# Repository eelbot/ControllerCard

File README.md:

#Pico Commander
The Pico Commander is a Circuit to PC interface that runs programs created by a user 
in a drag and drop style desktop application. This is my capstone project, and is currently
undergoing a major redesign. Throughout the first version of the project I learned a 
lot, and am going to improve Pico Commander in several areas to reduce cost, increase
functionality, and better the user experience.

## Version 0.1
Version 0.1 is the official release version presented as my capstone project. It
included the following functionality:
- Program creation on a PC through a drag and drop interface
- Program compilation and upload
- Program parsing and execution to control the digital I/O on the hardware module

Overall the project was a success. I bit off a little more than I could chew, and it went 
over budget, but for my first large-scale electronics project I am very happy.

## Version 0.2 (Moving Forward)
The next several releases will be different than what is currently in the
repo. Below are some of the changes that I am in the midst of planning.
- Reduce the number of digital I/O, but increase the available voltage
- Include 2 analog inputs. Low sample rate, but high accuracy
- Change microcontroller to increase energy efficiency and cost
- Plan for add-on boards

## Documentation and Reports
All current documentation and reports can be found at 
[eelbot.github.io/PicoCommander](https://eelbot.github.io/PicoCommander/)

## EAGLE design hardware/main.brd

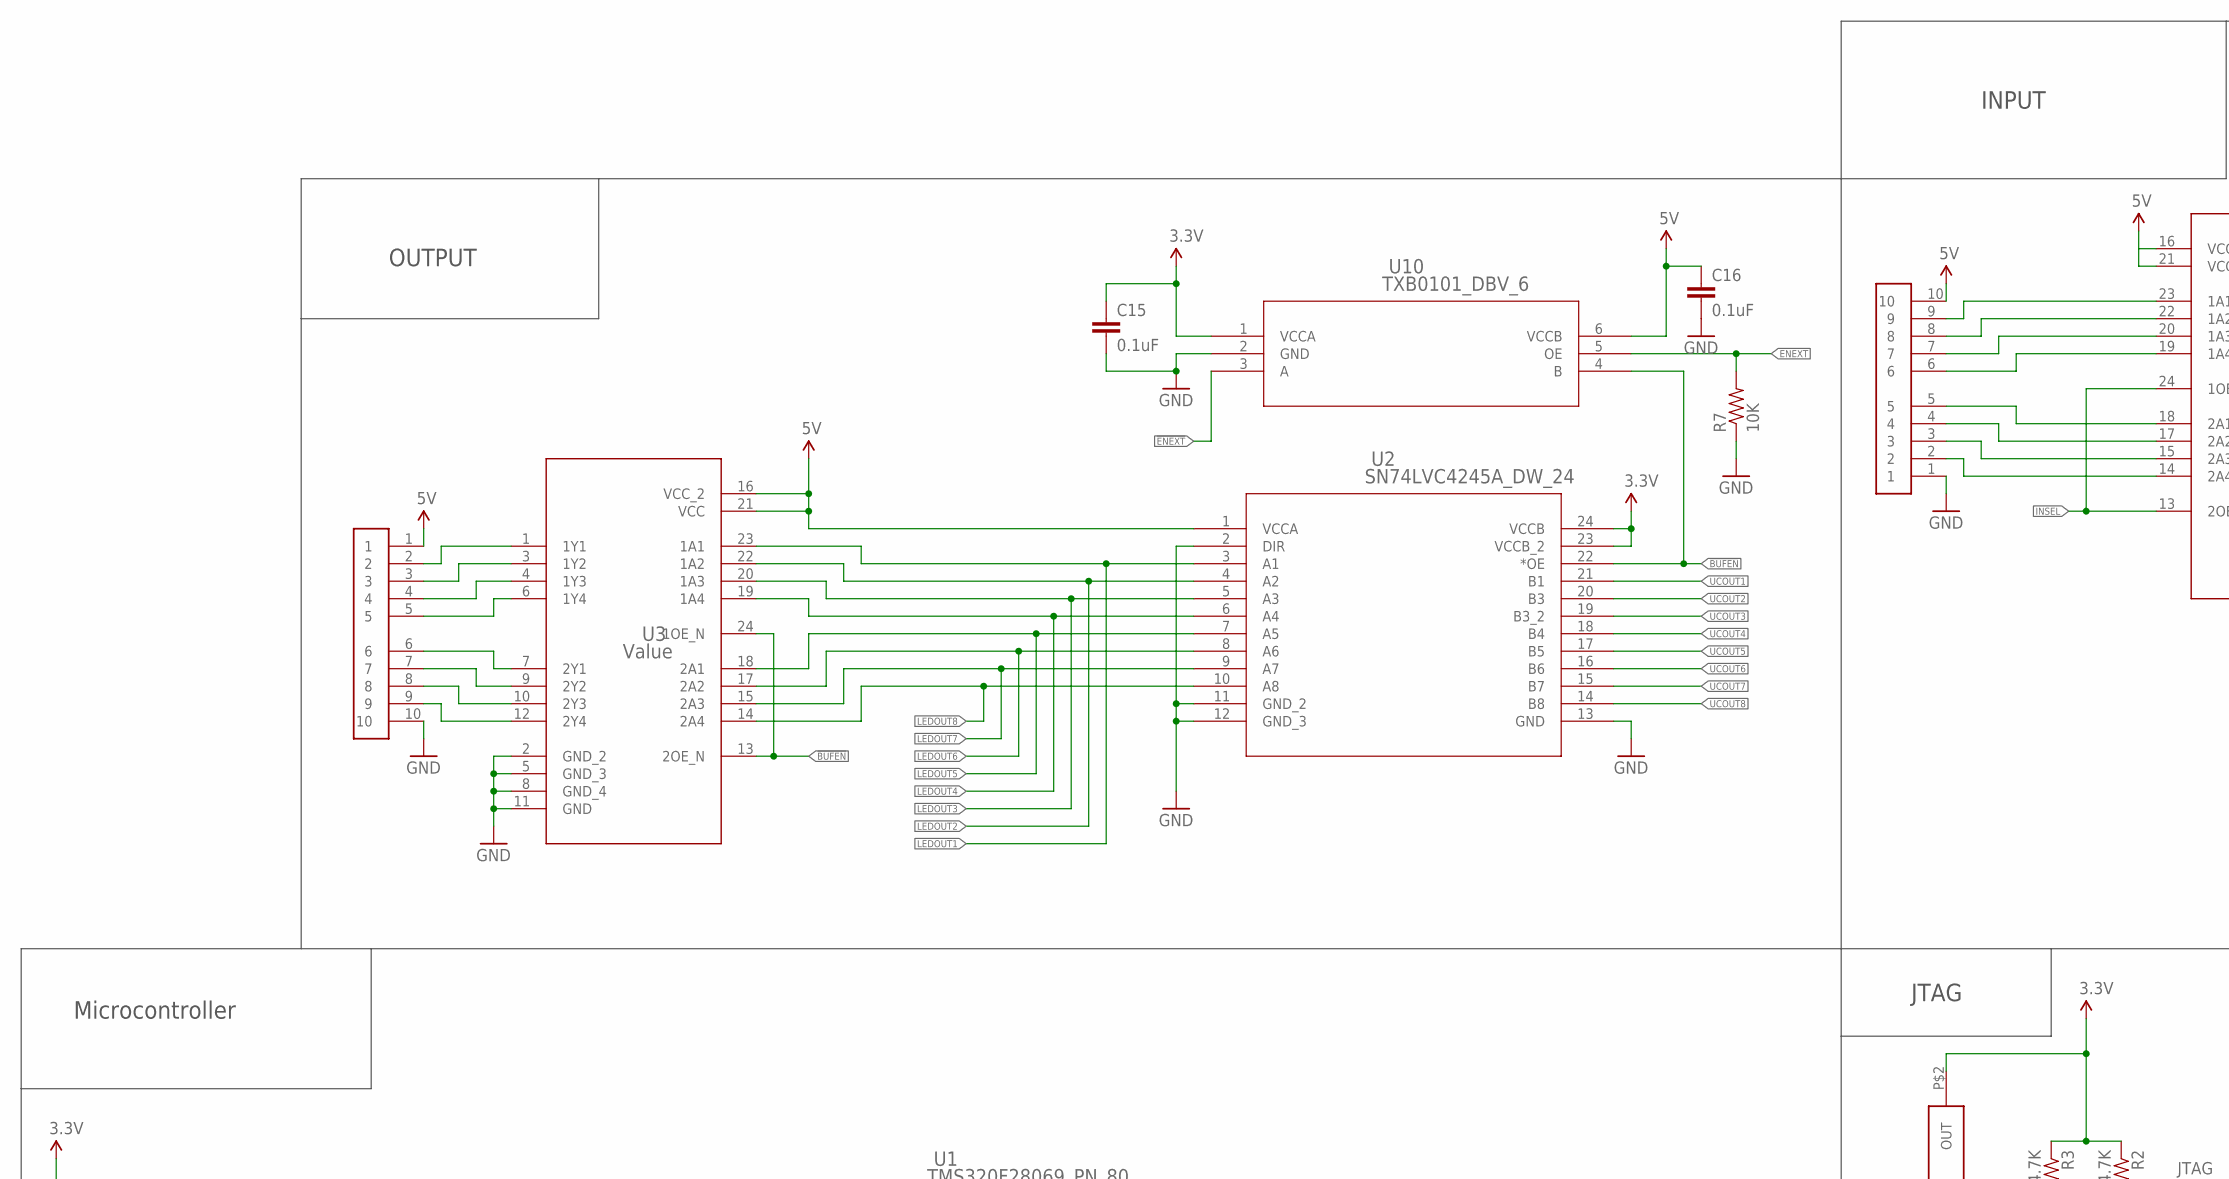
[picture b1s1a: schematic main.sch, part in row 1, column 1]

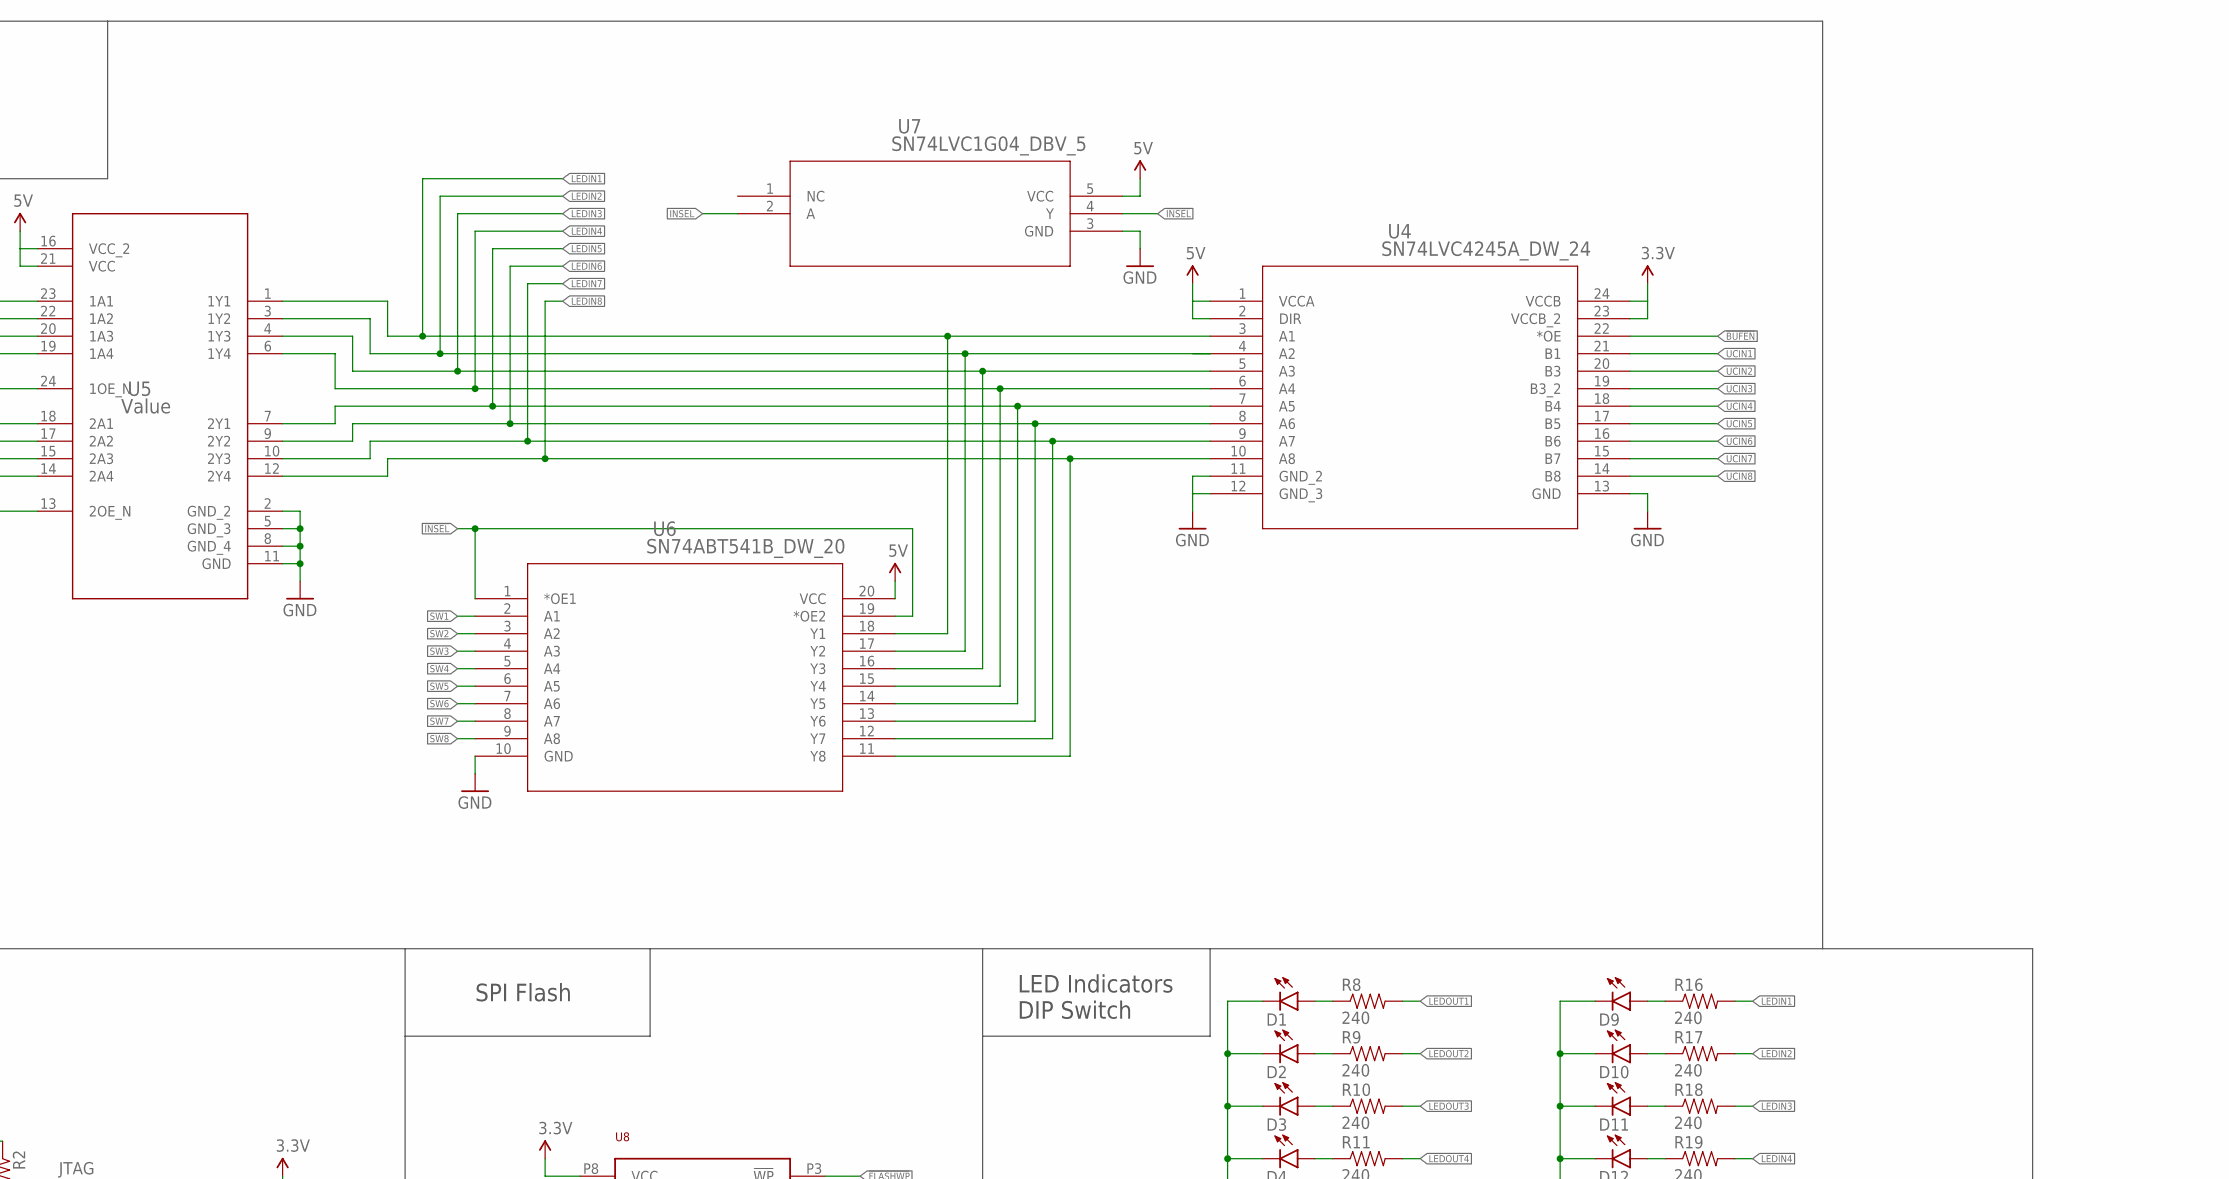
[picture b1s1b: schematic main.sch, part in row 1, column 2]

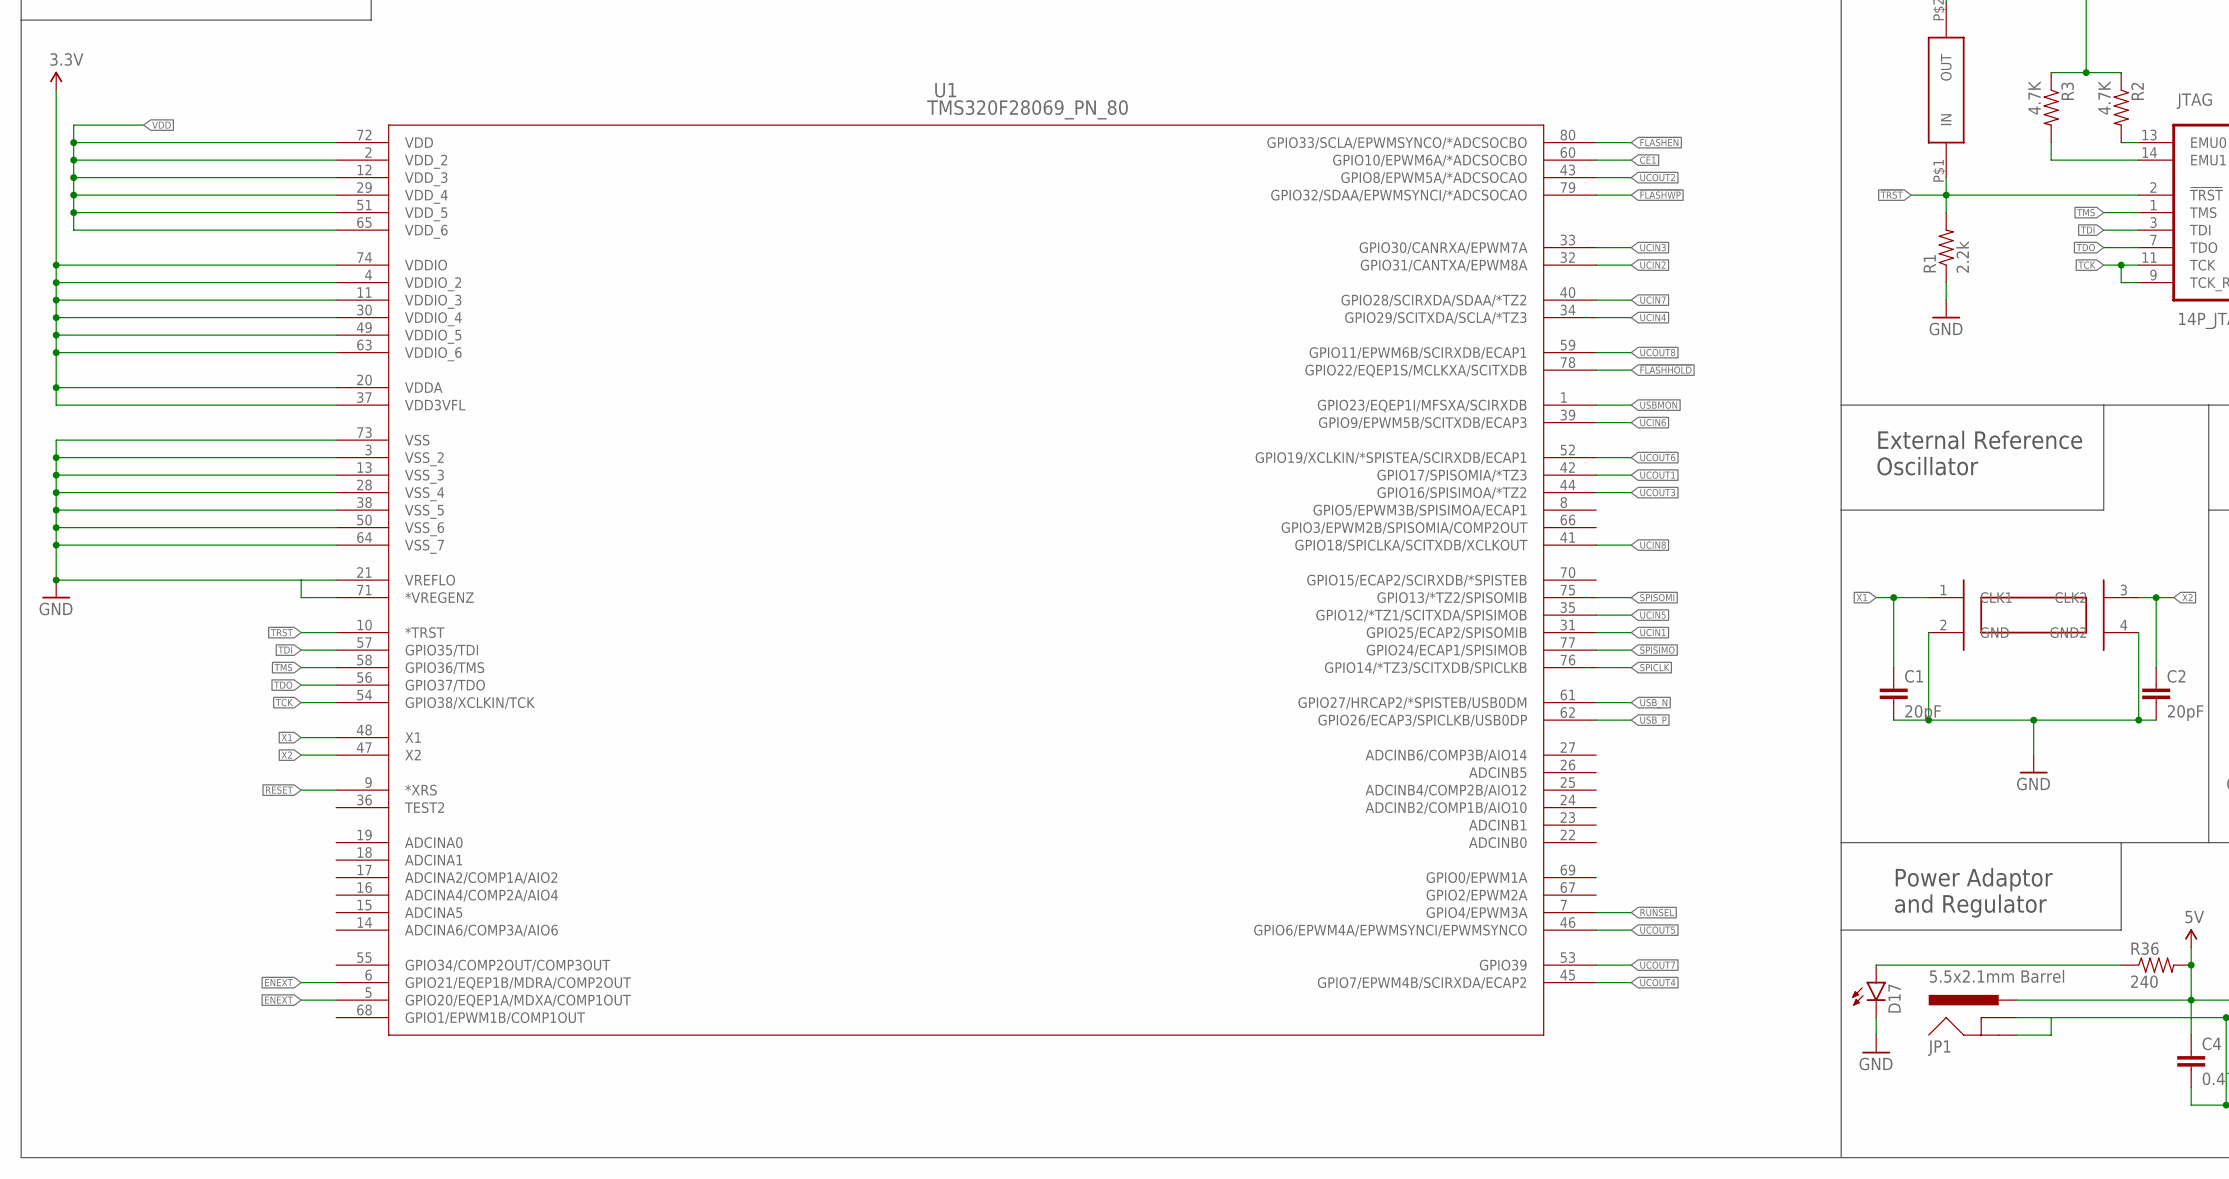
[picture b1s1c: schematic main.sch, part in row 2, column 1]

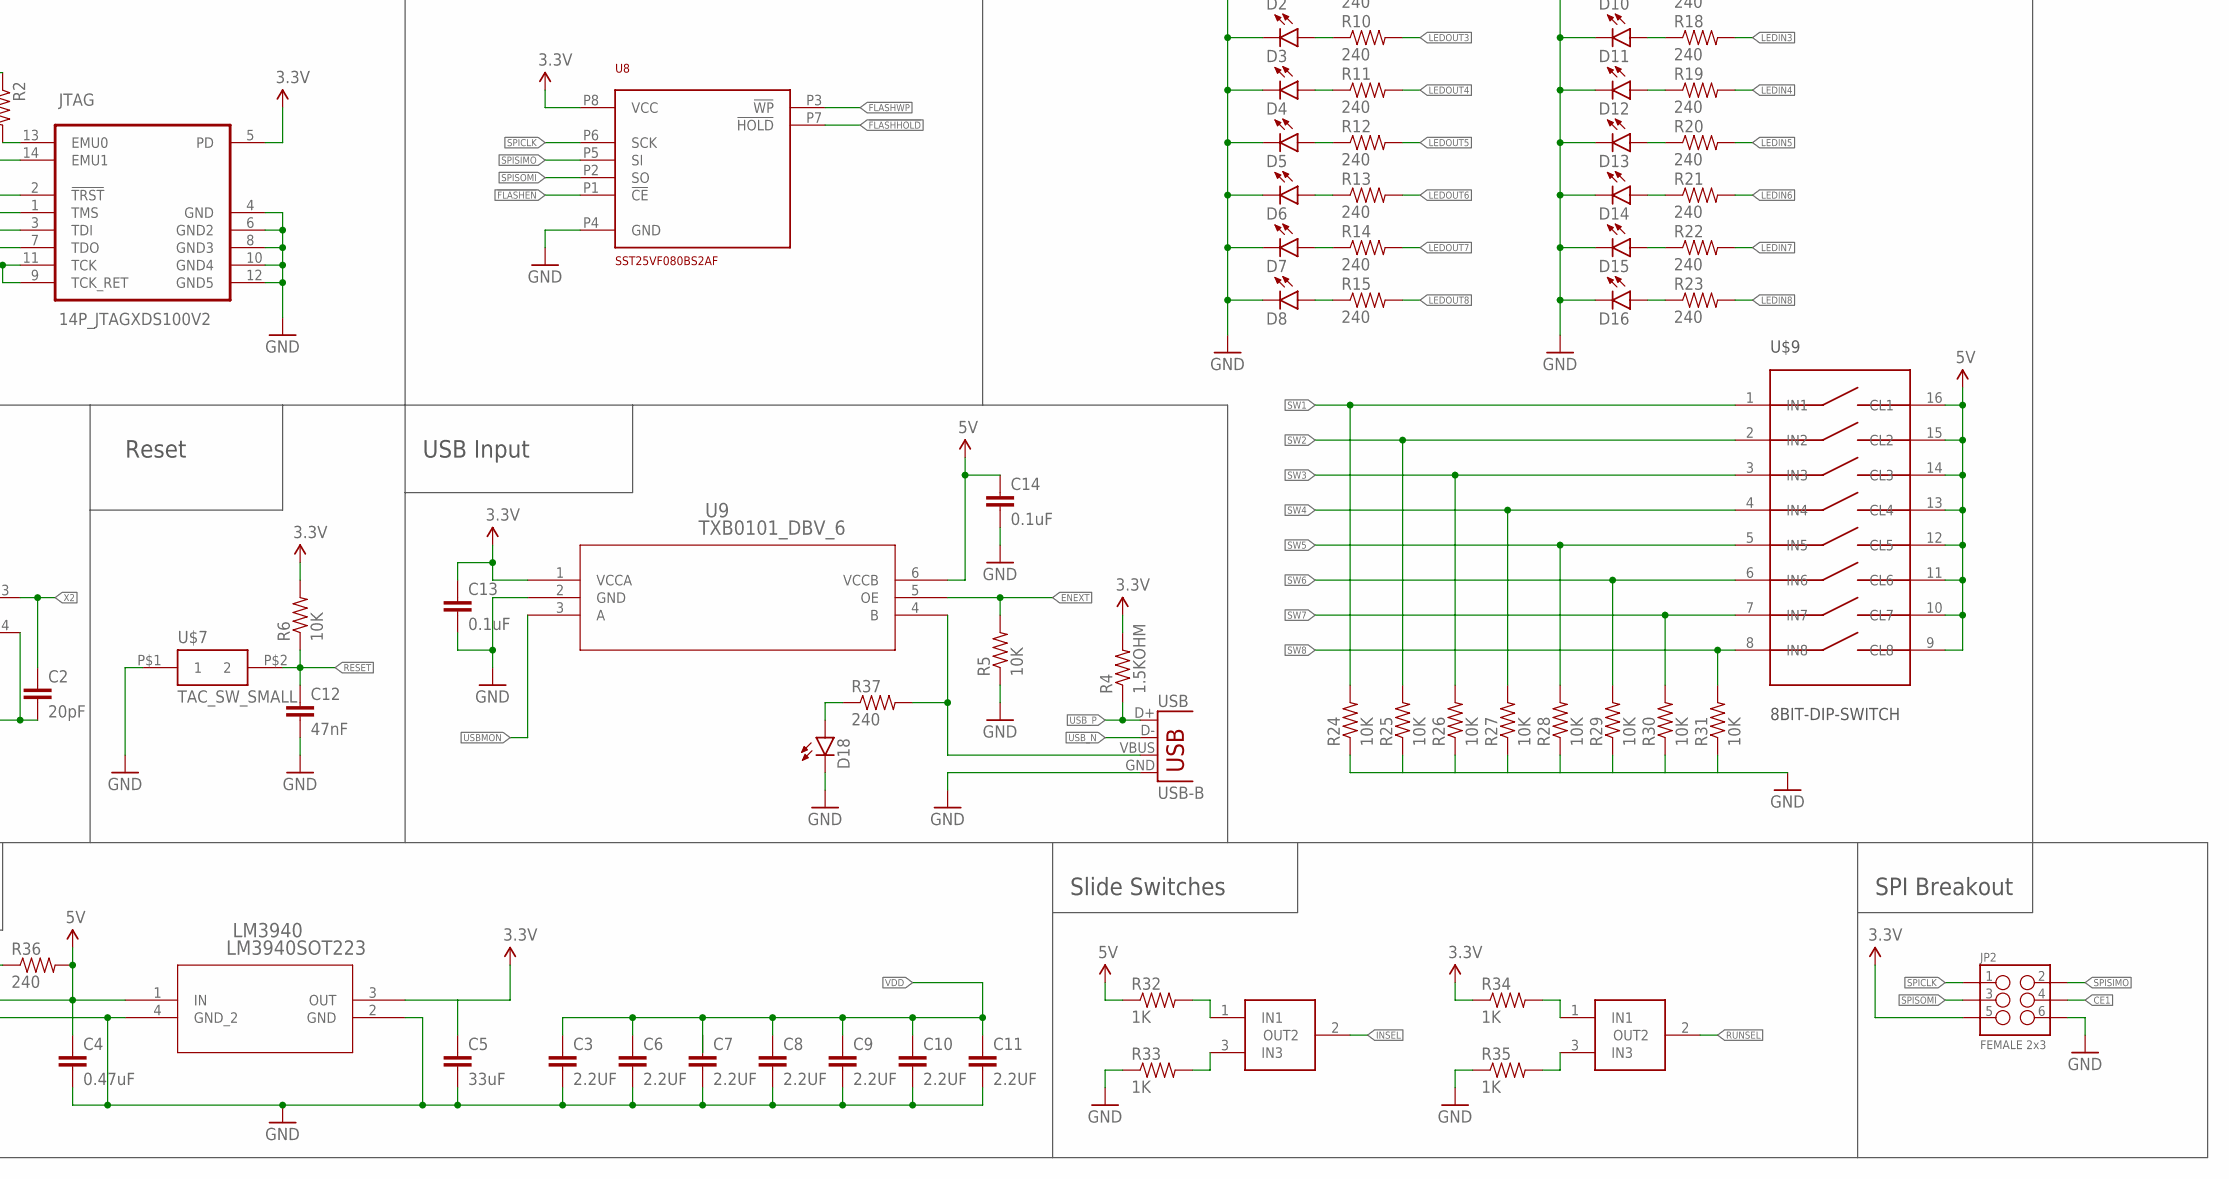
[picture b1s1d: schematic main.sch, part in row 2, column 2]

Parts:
!TRST!: DIP_SWITCH_1B; CHS-01B
C1, C2: 20pF; 0603-CAP
C3, C6, C7, C8, C9, C10, C11: 2.2UF; 1206
C4: 0.47uF; 0603-CAP
C5: 33uF; 1206
C12: 47nF; 0603-CAP
C13, C14, C15, C16: 0.1uF; 1206
CRYSTAL: CRYSTAL_SMD; 4SMD
D1, D2, D3, D4, D5, D6, D7, D8, D9, D10, D11, D12, D13, D14, D15, D16, D17, D18: LED3MM
JP1: 5.5x2.1mm Barrel; POWER_JACK_SMD
JP2: FEMALE 2x3; 2X3
JTAG: 14P_JTAGXDS100V2; 2X7
LM3940: LM3940SOT223; DCY
R1: 2.2k; 0603-RES
R2, R3: 4.7K; 0603-RES
R4: 1.5KOHM; 0603
R5, R6, R7, R24, R25, R26, R27, R28, R29, R30, R31: 10K; 0603-RES
R8, R9, R10, R11, R12, R13, R14, R15, R16, R17, R18, R19, R20, R21, R22, R23, R36, R37: 240; 0603-RES
R32, R33, R34, R35: 1K; 0603-RES
SW1, SW2: USER_SLIDE; USER_SLIDE_SWITCH
U1: TMS320F28069_PN_80; PN80
U2, U4: SN74LVC4245A_DW_24; DW24
U3, U5: Value; DW0024A_N
U6: SN74ABT541B_DW_20; DW20
U7: SN74LVC1G04_DBV_5; DBV5
U8: SST25VF080BS2AF; S2AE/F
U9, U10: TXB0101_DBV_6; DBV6
U$4, U$8: 8PIN_SOCKET; CONN-8PIN
U$7: TAC_SW_SMALL; 1000P
U$9: 8BIT-DIP-SWITCH; SPST-DIPS-SW
USB: USB-B; USB-B-PTH

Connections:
3.3V: !TRST!.P$2 (OUT), C5.1, C13.1, C15.1, JP2.5, JTAG.5 (PD), LM3940.3 (OUT), R2.1, R3.1, R4.2, R6.2, R34.1, U1.4 (VDDIO_2), U1.11 (VDDIO_3), U1.20 (VDDA), U1.30 (VDDIO_4), U1.37 (VDD3VFL), U1.49 (VDDIO_5), U1.63 (VDDIO_6), U1.74 (VDDIO), U2.23 (VCCB_2), U2.24 (VCCB), U4.23 (VCCB_2), U4.24 (VCCB), U8.P8 (VCC), U9.1 (VCCA), U10.1 (VCCA)
5V: C4.1, C14.1, C16.1, JP1.VIN0 (PWR), LM3940.1 (IN), R32.1, R36.2, U2.1 (VCCA), U3.16 (VCC_2), U3.21 (VCC), U4.1 (VCCA), U4.2 (DIR), U5.16 (VCC_2), U5.21 (VCC), U6.20 (VCC), U7.5 (VCC), U9.6 (VCCB), U10.6 (VCCB), U$4.1, U$8.10, U$9.9 (CL8), U$9.10 (CL7), U$9.11 (CL6), U$9.12 (CL5), U$9.13 (CL4), U$9.14 (CL3), U$9.15 (CL2), U$9.16 (CL1)
!BUFEN!: U2.22 (*OE), U3.13 (2OE_N), U3.24 (1OE_N), U4.22 (*OE), U10.4 (B)
!ENEXT!: U1.6 (GPIO21/EQEP1B/MDRA/COMP2OUT), U10.3 (A)
!FLASHEN!: U1.80 (GPIO33/SCLA/EPWMSYNCO/*ADCSOCBO), U8.P1 (!CE!)
!FLASHHOLD!: U1.78 (GPIO22/EQEP1S/MCLKXA/SCITXDB), U8.P7 (!HOLD!)
!FLASHWP!: U1.79 (GPIO32/SDAA/EPWMSYNCI/*ADCSOCAO), U8.P3 (!WP!)
!INSEL!: U6.1 (*OE1), U6.19 (*OE2), U7.4 (Y)
!TRST!: !TRST!.P$1 (IN), JTAG.2 (!TRST!), R1.2, U1.10 (*TRST)
CE1: JP2.4, U1.60 (GPIO10/EPWM6A/*ADCSOCBO)
ENEXT: R5.2, R7.2, U1.5 (GPIO20/EQEP1A/MDXA/COMP1OUT), U9.5 (OE), U10.5 (OE)
GND: C1.2, C2.2, C3.2, C4.2, C5.2, C6.2, C7.2, C8.2, C9.2, C10.2, C11.2, C12.2, C13.2, C14.2, C15.2, C16.2, CRYSTAL.2 (GND), CRYSTAL.4 (GND2), D1.K (C), D2.K (C), D3.K (C), D4.K (C), D5.K (C), D6.K (C), D7.K (C), D8.K (C), D9.K (C), D10.K (C), D11.K (C), D12.K (C), D13.K (C), D14.K (C), D15.K (C), D16.K (C), D17.K (C), D18.K (C), JP1.GND (GNDBREAK), JP1.P$4 (GND), JP2.6, JTAG.4 (GND), JTAG.6 (GND2), JTAG.8 (GND3), JTAG.10 (GND4), JTAG.12 (GND5), LM3940.2 (GND), LM3940.4 (GND_2), R1.1, R5.1, R7.1, R24.1, R25.1, R26.1, R27.1, R28.1, R29.1, R30.1, R31.1, R33.1, R35.1, U1.3 (VSS_2), U1.13 (VSS_3), U1.21 (VREFLO), U1.28 (VSS_4), U1.38 (VSS_5), U1.50 (VSS_6), U1.64 (VSS_7), U1.71 (*VREGENZ), U1.73 (VSS), U2.2 (DIR), U2.11 (GND_2), U2.12 (GND_3), U2.13 (GND), U3.2 (GND_2), U3.5 (GND_3), U3.8 (GND_4), U3.11 (GND), U4.11 (GND_2), U4.12 (GND_3), U4.13 (GND), U5.2 (GND_2), U5.5 (GND_3), U5.8 (GND_4), U5.11 (GND), U6.10 (GND), U7.3 (GND), U8.P4 (GND), U9.2 (GND), U10.2 (GND), U$4.10, U$7.P$1 (1), U$8.1, USB.GND
INSEL: SW1.2 (OUT2), U5.13 (2OE_N), U5.24 (1OE_N), U7.2 (A)
LEDIN1: R16.2, U4.3 (A1), U5.1 (1Y1), U6.18 (Y1)
LEDIN2: R17.2, U4.4 (A2), U5.3 (1Y2), U6.17 (Y2)
LEDIN3: R18.2, U4.5 (A3), U5.4 (1Y3), U6.16 (Y3)
LEDIN4: R19.2, U4.6 (A4), U5.6 (1Y4), U6.15 (Y4)
LEDIN5: R20.2, U4.7 (A5), U5.7 (2Y1), U6.14 (Y5)
LEDIN6: R21.2, U4.8 (A6), U5.9 (2Y2), U6.13 (Y6)
LEDIN7: R22.2, U4.9 (A7), U5.10 (2Y3), U6.12 (Y7)
LEDIN8: R23.2, U4.10 (A8), U5.12 (2Y4), U6.11 (Y8)
LEDOUT1: R8.2, U2.3 (A1), U3.23 (1A1)
LEDOUT2: R9.2, U2.4 (A2), U3.22 (1A2)
LEDOUT3: R10.2, U2.5 (A3), U3.20 (1A3)
LEDOUT4: R11.2, U2.6 (A4), U3.19 (1A4)
LEDOUT5: R12.2, U2.7 (A5), U3.18 (2A1)
LEDOUT6: R13.2, U2.8 (A6), U3.17 (2A2)
LEDOUT7: R14.2, U2.9 (A7), U3.15 (2A3)
LEDOUT8: R15.2, U2.10 (A8), U3.14 (2A4)
unnamed: R37.2, U9.4 (B), USB.VBUS
unnamed: JTAG.14 (EMU1), R3.2
unnamed: JTAG.13 (EMU0), R2.2
unnamed: D1.A, R8.1
unnamed: D2.A, R9.1
unnamed: D3.A, R10.1
unnamed: D4.A, R11.1
unnamed: D5.A, R12.1
unnamed: D6.A, R13.1
unnamed: D7.A, R14.1
unnamed: D8.A, R15.1
unnamed: U3.1 (1Y1), U$4.2
unnamed: U3.3 (1Y2), U$4.3
unnamed: U3.4 (1Y3), U$4.4
unnamed: U3.6 (1Y4), U$4.5
unnamed: U3.12 (2Y4), U$4.9
unnamed: U3.10 (2Y3), U$4.8
unnamed: U3.9 (2Y2), U$4.7
unnamed: U3.7 (2Y1), U$4.6
unnamed: U5.23 (1A1), U$8.9
unnamed: U5.22 (1A2), U$8.8
unnamed: U5.20 (1A3), U$8.7
unnamed: U5.19 (1A4), U$8.6
unnamed: U5.14 (2A4), U$8.2
unnamed: U5.15 (2A3), U$8.3
unnamed: U5.17 (2A2), U$8.4
unnamed: U5.18 (2A1), U$8.5
unnamed: R33.2, SW1.3 (IN3)
unnamed: D9.A, R16.1
unnamed: D10.A, R17.1
unnamed: D11.A, R18.1
unnamed: D12.A, R19.1
unnamed: D13.A, R20.1
unnamed: D14.A, R21.1
unnamed: D15.A, R22.1
unnamed: D16.A, R23.1
unnamed: R32.2, SW1.1 (IN1)
unnamed: R34.2, SW2.1 (IN1)
unnamed: R35.2, SW2.3 (IN3)
unnamed: D17.A, R36.1
unnamed: D18.A, R37.1
RESET: C12.1, R6.1, U1.9 (*XRS), U$7.P$2 (2)
RUNSEL: SW2.2 (OUT2), U1.7 (GPIO4/EPWM3A)
SPICLK: JP2.1, U1.76 (GPIO14/*TZ3/SCITXDB/SPICLKB), U8.P6 (SCK)
SPISIMO: JP2.2, U1.77 (GPIO24/ECAP1/SPISIMOB), U8.P5 (SI)
SPISOMI: JP2.3, U1.75 (GPIO13/*TZ2/SPISOMIB), U8.P2 (SO)
SW1: R24.2, U6.2 (A1), U$9.1 (IN1)
SW2: R25.2, U6.3 (A2), U$9.2 (IN2)
SW3: R26.2, U6.4 (A3), U$9.3 (IN3)
SW4: R27.2, U6.5 (A4), U$9.4 (IN4)
SW5: R28.2, U6.6 (A5), U$9.5 (IN5)
SW6: R29.2, U6.7 (A6), U$9.6 (IN6)
SW7: R30.2, U6.8 (A7), U$9.7 (IN7)
SW8: R31.2, U6.9 (A8), U$9.8 (IN8)
TCK: JTAG.9 (TCK_RET), JTAG.11 (TCK), U1.54 (GPIO38/XCLKIN/TCK)
TDI: JTAG.3 (TDI), U1.57 (GPIO35/TDI)
TDO: JTAG.7 (TDO), U1.56 (GPIO37/TDO)
TMS: JTAG.1 (TMS), U1.58 (GPIO36/TMS)
UCIN1: U1.31 (GPIO25/ECAP2/SPISOMIB), U4.21 (B1)
UCIN2: U1.32 (GPIO31/CANTXA/EPWM8A), U4.20 (B3)
UCIN3: U1.33 (GPIO30/CANRXA/EPWM7A), U4.19 (B3_2)
UCIN4: U1.34 (GPIO29/SCITXDA/SCLA/*TZ3), U4.18 (B4)
UCIN5: U1.35 (GPIO12/*TZ1/SCITXDA/SPISIMOB), U4.17 (B5)
UCIN6: U1.39 (GPIO9/EPWM5B/SCITXDB/ECAP3), U4.16 (B6)
UCIN7: U1.40 (GPIO28/SCIRXDA/SDAA/*TZ2), U4.15 (B7)
UCIN8: U1.41 (GPIO18/SPICLKA/SCITXDB/XCLKOUT), U4.14 (B8)
UCOUT1: U1.42 (GPIO17/SPISOMIA/*TZ3), U2.21 (B1)
UCOUT2: U1.43 (GPIO8/EPWM5A/*ADCSOCAO), U2.20 (B3)
UCOUT3: U1.44 (GPIO16/SPISIMOA/*TZ2), U2.19 (B3_2)
UCOUT4: U1.45 (GPIO7/EPWM4B/SCIRXDA/ECAP2), U2.18 (B4)
UCOUT5: U1.46 (GPIO6/EPWM4A/EPWMSYNCI/EPWMSYNCO), U2.17 (B5)
UCOUT6: U1.52 (GPIO19/XCLKIN/*SPISTEA/SCIRXDB/ECAP1), U2.16 (B6)
UCOUT7: U1.53 (GPIO39), U2.15 (B7)
UCOUT8: U1.59 (GPIO11/EPWM6B/SCIRXDB/ECAP1), U2.14 (B8)
USBMON: U1.1 (GPIO23/EQEP1I/MFSXA/SCIRXDB), U9.3 (A)
USB_N: U1.61 (GPIO27/HRCAP2/*SPISTEB/USB0DM), USB.D-
USB_P: R4.1, U1.62 (GPIO26/ECAP3/SPICLKB/USB0DP), USB.D+
VDD: C3.1, C6.1, C8.1, C9.1, C10.1, C11.1, U1.2 (VDD_2), U1.12 (VDD_3), U1.29 (VDD_4), U1.51 (VDD_5), U1.65 (VDD_6), U1.72 (VDD)
X1: C1.1, CRYSTAL.1 (CLK1), U1.48 (X1)
X2: C2.1, CRYSTAL.3 (CLK2), U1.47 (X2)

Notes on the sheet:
JTAG
External Reference Oscillator
Reset
Power Adaptor and Regulator
USB Input
SPI Flash
INPUT
OUTPUT
Microcontroller
LED Indicators DIP Switch
Slide Switches
SPI Breakout

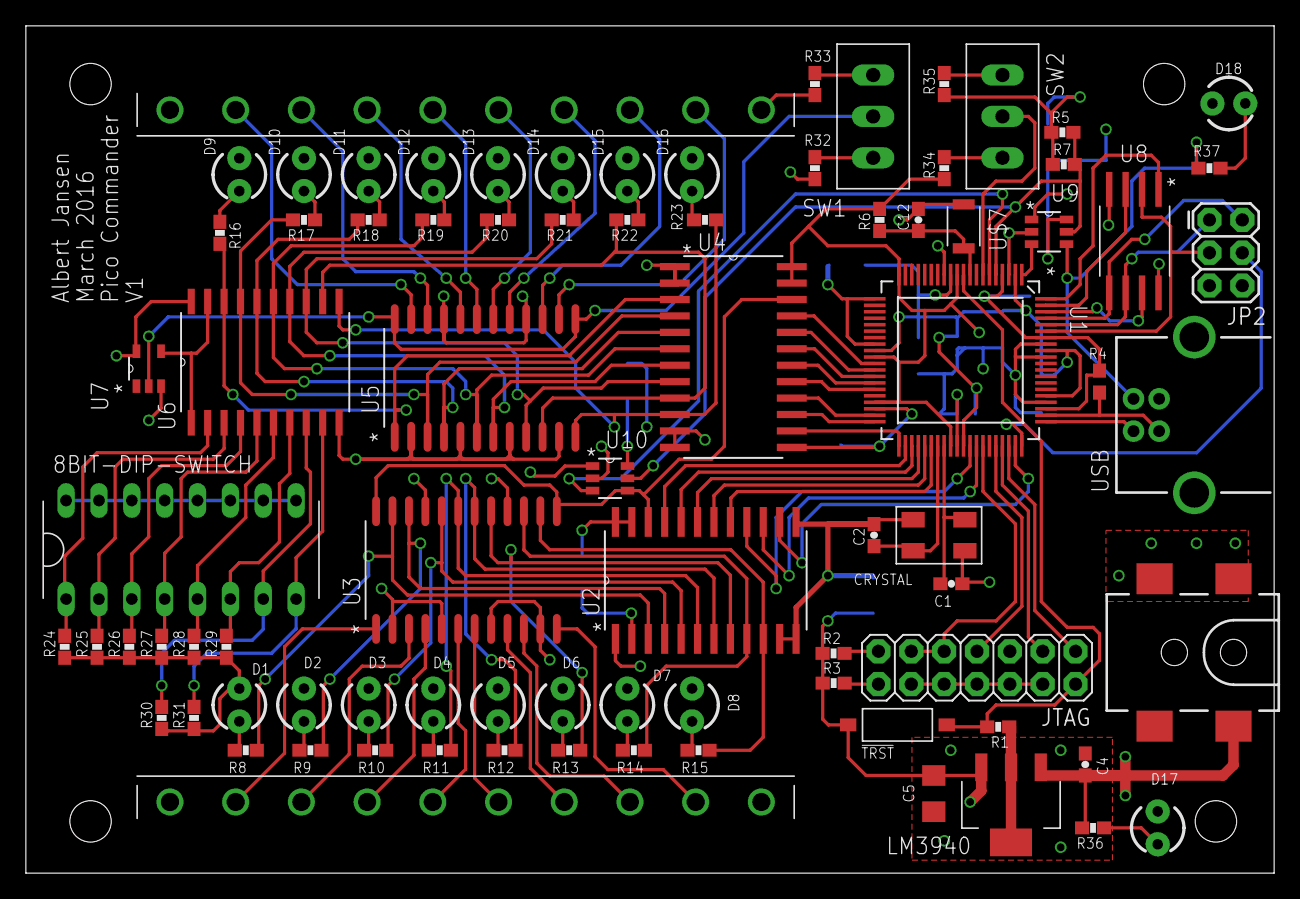
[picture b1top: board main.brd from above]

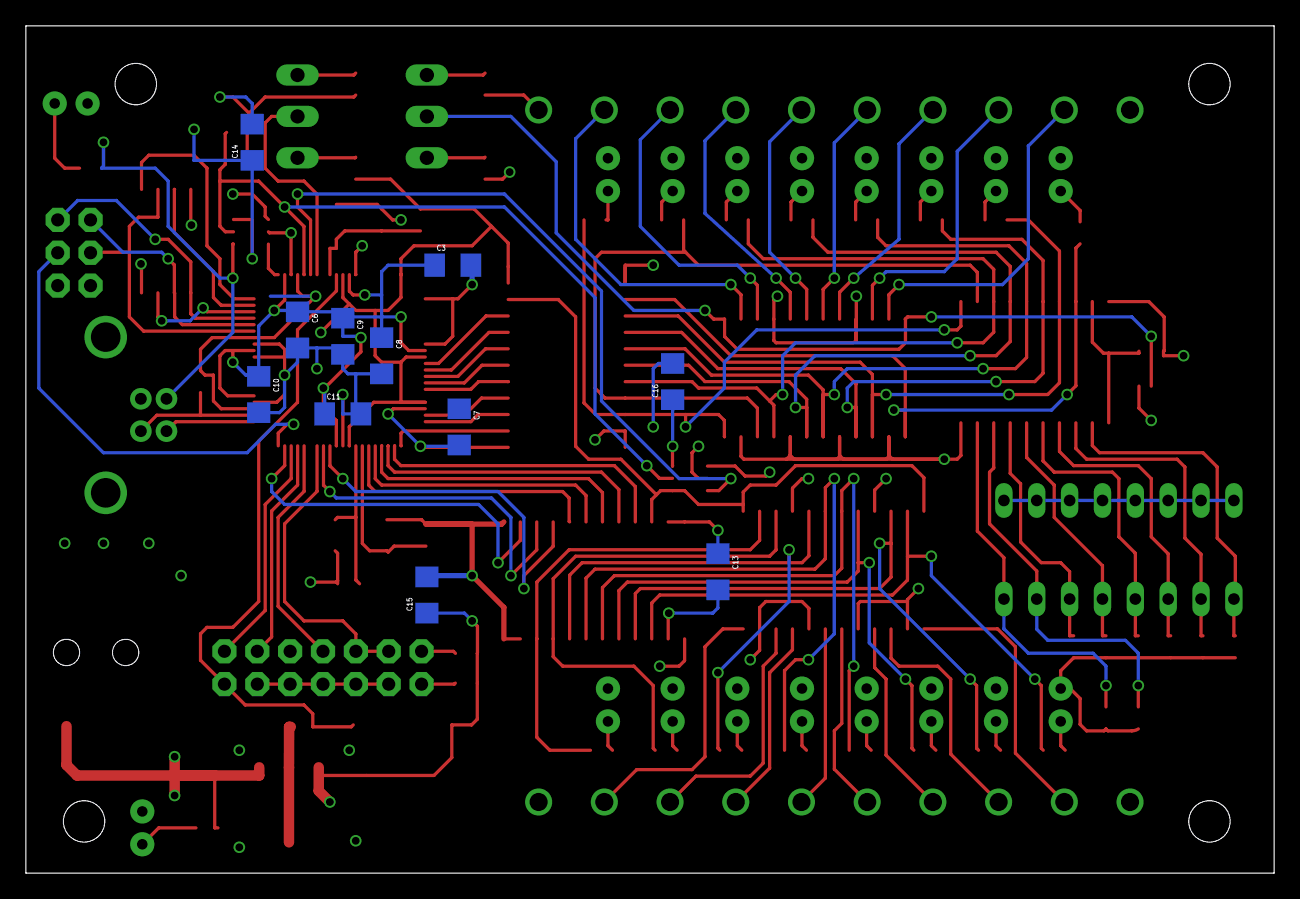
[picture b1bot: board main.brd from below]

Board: 4 copper layers, 96.5 x 65.5 mm, 94 parts (11 on the bottom side), 109 nets.

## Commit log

2015-10-22 Initial setup and basic info page
2015-10-22 First main page setup commit
2015-10-22 Testing deletion and branches
2015-10-22 Removed some info from pre-proposal
2016-02-26 First commit. Basic GUI, hardware schematic almost complete
2016-02-27 Finished schematic, laid out board
2016-02-27 Initializing README
2016-02-27 Updated to resolve future merge conflicts (README)
2016-02-28 Began routing
2016-02-29 Finished routing SPI Flash and Output section. Re-wired parts of the input section.
2016-02-29 Updated input ribbon connector schematic, began to route input analog switches
2016-03-01 Ripped up USB routing, SPI routing, and previously made input stage routing. Starting over.
2016-03-01 Beginning new layout and routing. Clock traces and USB routed first.
2016-03-02 Added repo link, changed link styles
2016-03-02 Brief test
2016-03-03 Updated site with change of name, lighter color palate. Changed from pre-proposal document to proposal document
2016-03-03 Minor file changes and running the program
2016-03-04 Change analog switch for input selection to buffer. Reviewed and reworked enable pin logic. Added single NOT gate and 5V buffer to ControllerCard library
2016-03-04 Finished routing part of the board. Rearranged input connector in schematic.
2016-03-07 Changed ribbon cable connectors to components on the board. Added DIP switch, LED's. Re-arranged components, started routing.
2016-03-07 Routed part of output LED section
2016-03-08 Routed the output section. Ripped up SPI section. Finished routing input section.
2016-03-08 Arranged and began routing DIP switches
2016-03-09 Finished routing all signals traces. 3Vcc, 5Vcc, GND not yet routed. Signal traces need to be reviewed and cleaned up.
2016-03-09 Finished re-routing clock and JTAG. Begun re-route of output stage.
2016-03-09 Finished cleaning up routing. Updated user connectors to have 10 pins.
2016-03-10 Checked and edited component layouts. Updated and checked passive component values. Double checked chip peripherals.
2016-03-11 Finished routing board. Finished cleaning up silkscreen (top).
2016-03-11 Quick merge test
2016-03-11 Fixed minor error with JTAG. TRST pin not connected
2016-03-11 Routed un-noticed airwires. Tried to add SPI breakout. Unsuccessful
2016-03-11 Added SPI breakout. Routed and updated silkscreen for SPI breakout
2016-03-11 DRC fixes with extra room
2016-03-11 Final of v1. Sent to fab house. DRC and minor silkscreen updates
2016-03-15 Created 'Open File' and 'New Blank File' functions. Updated comments and fileop.py code.
2016-03-17 Bugfixes on open function, almost completed the save function
2016-03-18 Finished save and save as function
2016-03-19 Code clean up and simplification. Need to add 'Double Click to open' to file browser
2016-03-19 Tested using qApp. Does not work
2016-03-19 Further qApp tests
2016-03-30 Added error log
2016-03-30 Updated connections to include nets. Fixed connection problem between VDD and VDDIO pins
2016-04-08 Added project development to branch
2016-04-09 Configured basic USB communication and serial/terminal emulation
2016-04-10 USB/COM port connection working. Fully functional RxHandler.
2016-04-10 Peripheral runtime and firmware add-ins. Not relevant to overall gui dev.
2016-04-10 Added toolbar. Started the serial connection functions. Completed the double click to open file function
2016-04-11 Added CodeStartBranch.asm in attempt to solve boot to flash error
2016-04-12 Added F2806x_CodeStartBranch.asm to solve problem of flash boot not working. Tested and functional
2016-04-12 Minor CCS Check
2016-04-12 Testing of file I/O
2016-04-14 Added workspace path change option, and updated syntax on openWork signal
2016-04-15 Fixed formatting for neatness (and PEP8). Added more comments, made old comments clearer
2016-04-16 Added basic drag and drop file format and functionality
2016-04-16 Updated tile functions, neatened code
2016-04-16 Generated executable file in py3.4 environemnt in Anaconda
2016-04-18 Minor Testing
2016-04-20 Updated and added comments and function descriptions
2016-04-21 Added preliminary arrow drawing functionality
2016-04-21 Test Updates
2016-04-22 Adding connections now works. Connections do not move when blocks do.
2016-04-23 Drag and drop visuals completed
2016-04-23 File operations added for drag and drop files
2016-04-23 Changed name from tile.py to entity.py to add distinction between file and object
2016-04-23 Added library import functionality
2016-04-24 Library import functionality complete. Cleaned up minor save file issues
2016-04-24 Set up compile function in menu, and ensured there is a file to compile
2016-04-25 Updated file to make function references hex
2016-04-25 Fixed bug where new arrows could not be drawn on an open file
2016-04-26 Added input and output variable selection when drawing arows. Program only asks user, doesn't save or open information. Information is also not added to the arrow
2016-04-27 Updated multiple inputs for arrows. Encountered bug when adding same lib multiple times. Not fixed.
2016-04-27 Fixed multiple lib add bug. Fixed null function assignment bug
2016-04-28 Fixed 'untitled' file bug. Ran tests for final report and guide
2016-04-29 Functions with multiple inputs work. Functions requiring a value work
2016-04-29 Compile function working correctly
2016-04-29 Serial connection beginning testing
2016-04-29 Small tests to ensure functionality post-merge
2016-04-29 Working on serial functionality
2016-04-30 Serial Upload is fully functional, program read is in place
2016-04-30 Output functionality works for small programs
2016-04-30 Fixed small issue with interpretation of Hex numbers
2016-05-01 Output functionality fixed to work on small programs
2016-05-01 Input now works at the most basic level
2016-05-01 Removed junk files from one time setup of CCS
2016-05-01 Added delete button functionality (CTRL+CLICK)
2016-05-01 Bugfixes and final funtionality touches before presentation
2016-05-01 Working code for presentation
2016-05-01 Small updates and testing
2016-05-01 Updated with final report
2016-05-01 Forgot to change title...
2016-05-04 Changed IDE. Going to try out IntelliJ for the Python side of things
2016-05-16 Removed unnecessary IntelliJ folder
2016-05-26 Removed tracking the __pycache__
2016-05-26 Updated to include a proper .gitignore (generic python)
2016-05-31 Updated with working .gitignore
2016-05-31 Updated to include current version and future development
2016-05-31 Added .gitignore
2016-06-01 Fixed link

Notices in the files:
parts and their libraries:
SparkFun-Capacitors: Licensing: Creative Commons ShareAlike 4.0 International - https://creativecommons.org/licenses/by-sa/4.0
